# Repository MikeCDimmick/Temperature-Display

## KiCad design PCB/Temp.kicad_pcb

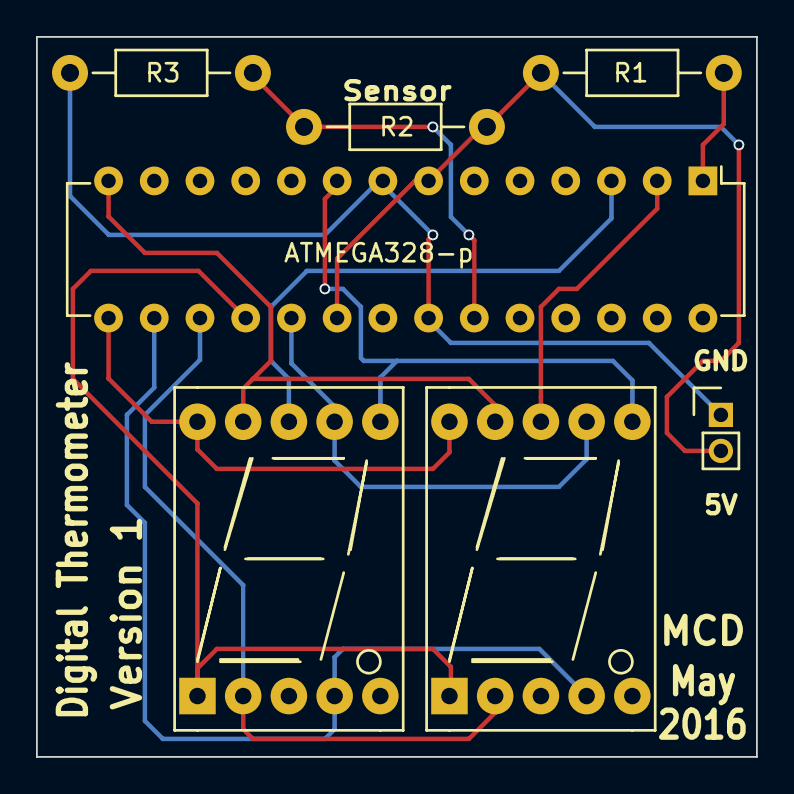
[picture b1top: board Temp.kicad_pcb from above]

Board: 2 copper layers, 40.0 x 40.0 mm, 4 parts (0 on the bottom side), 4 nets.

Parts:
ATMEGA328-p: ATMEGA328-P; DIP-28_W7.62mm
R1, R2, R3: 10k; Resistor_Horizontal_RM10mm

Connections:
+5V: ATMEGA328-p.7, ATMEGA328-p.20, R1.1, R2.1
GND: ATMEGA328-p.8, ATMEGA328-p.22, R3.2
unnamed: ATMEGA328-p.1, R1.2
unnamed: ATMEGA328-p.23, R2.2, R3.1
